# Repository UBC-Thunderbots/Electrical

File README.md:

# Electrical

Our repository for all things electrical! To get started, please see the [getting started document](docs/getting-started/getting-started.md).

If you are already set up, go to the [electrical system overview](docs/getting-started/board-overview.md).

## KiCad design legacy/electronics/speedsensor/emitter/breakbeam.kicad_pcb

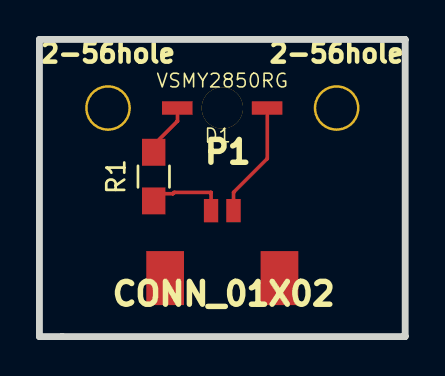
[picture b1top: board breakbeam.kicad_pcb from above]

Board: 2 copper layers, 20.3 x 16.5 mm, 5 parts (0 on the bottom side), 3 nets.

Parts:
2-56hole, 2-56hole#2: P***; 2-56hole
D1: VSMY2850RG; LED-VSMY2850RG
P1: CONN_01X02; connector_0_49_in_2pin
R1: 16.5R; R_0805_HandSoldering

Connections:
/3.3v: P1.1, R1.1
/GND: D1.1, P1.2
unnamed: D1.2, R1.2

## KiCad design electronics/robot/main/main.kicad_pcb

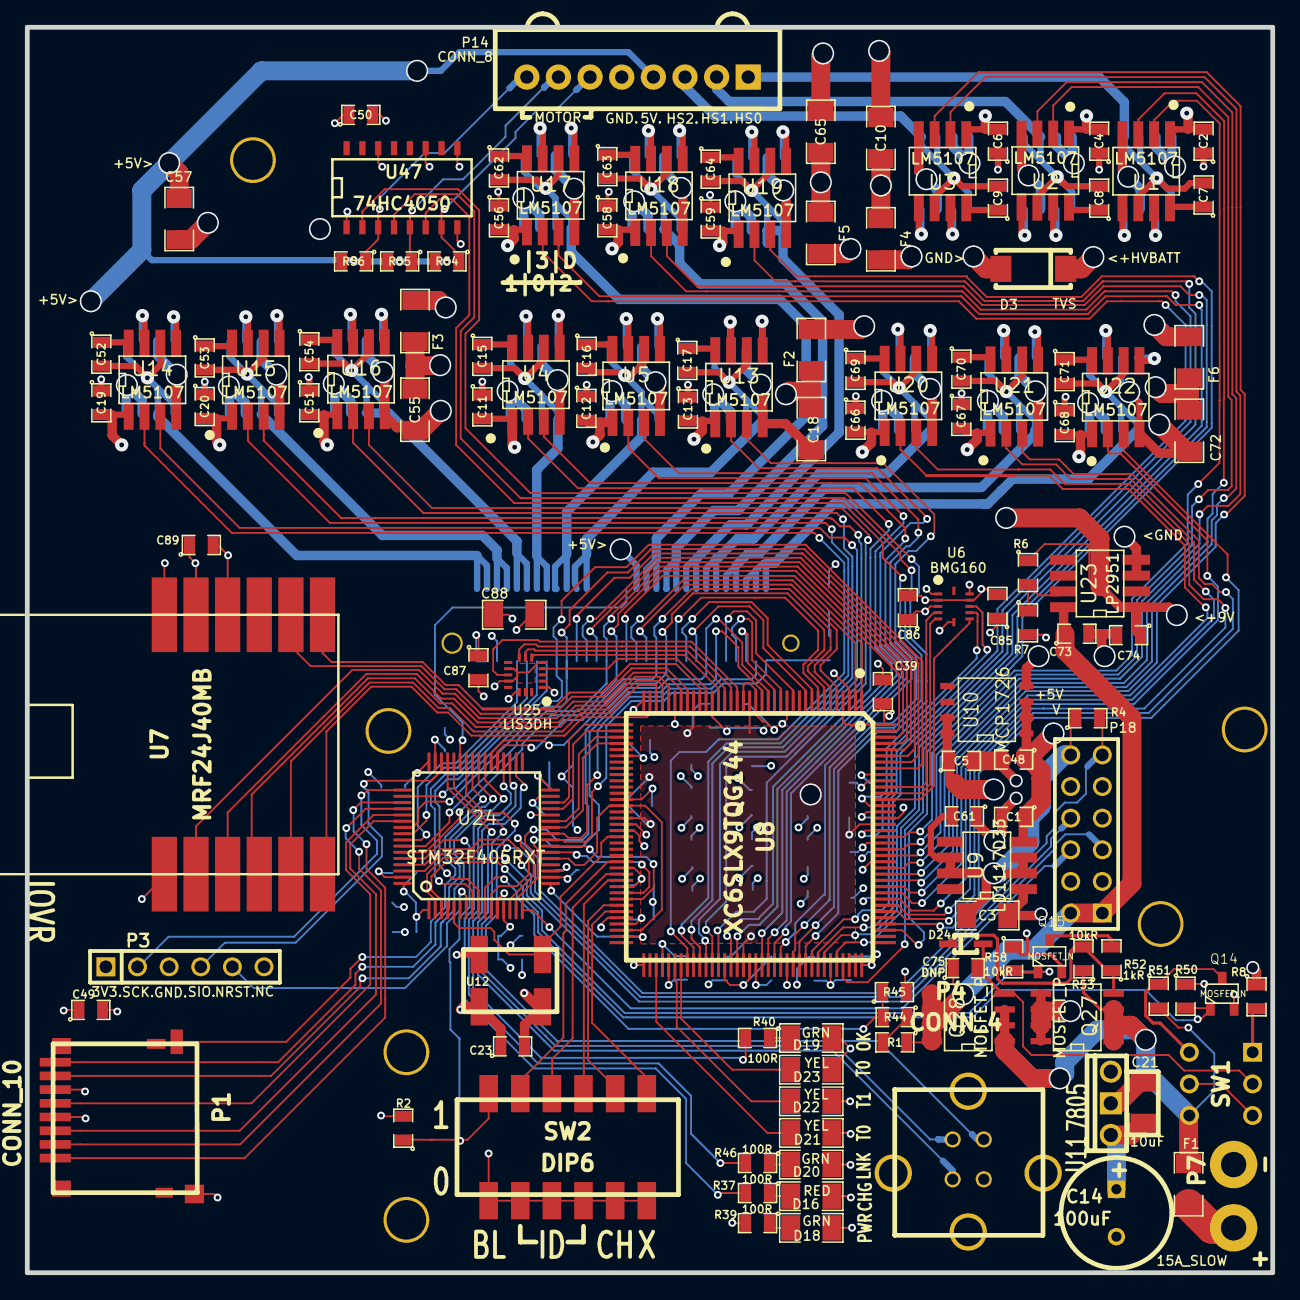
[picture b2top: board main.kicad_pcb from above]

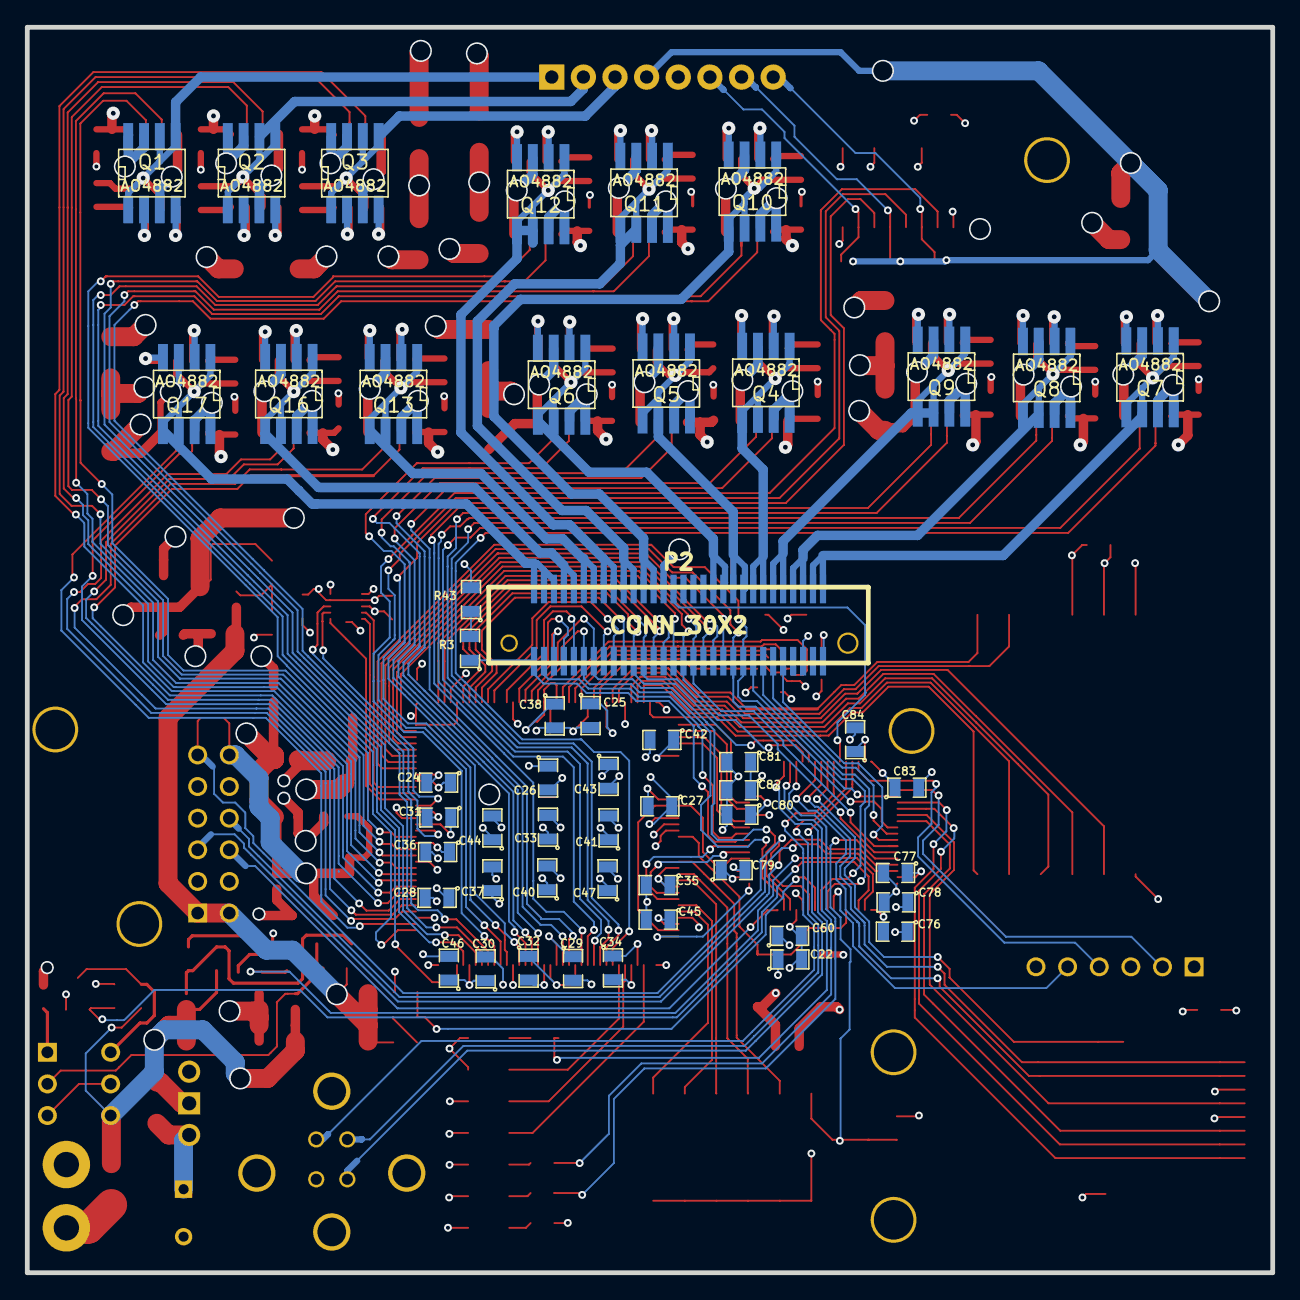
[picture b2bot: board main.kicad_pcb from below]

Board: 4 copper layers, 100.0 x 100.0 mm, 186 parts (52 on the bottom side), 210 nets.

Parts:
C1, C2, C4, C6, C7, C8, C9, C11, C12, C13, C15, C16, C17, C19, C20, C22, C23, C49, C50, C51, C52, C53, C54, C56, C58, C59, C61, C62, C63, C64, C66, C67, C68, C69, C70, C71, C76, C77, C79, C81, C83, C85, C86, C87, C89: 100nF; SM0805
C3, C10, C18, C21, C55, C57, C65, C72, C88: 10uF; SM1206
C5, C48, C73, C74, C75: 1uF; SM0805
C14: 100uF; C1.5V8V
C24, C25, C26, C27, C28, C29, C30, C32, C33, C34, C35, C37, C39, C41, C78, C82: 4.7uF; SM0805
C31, C36, C38, C40, C42, C43, C44, C45, C46, C47: 470nF; SM0805
C60: 10nF; SM0805
C80, C84: 2.2uF; SM0805
D3: TVS; DO-214AC
D16: RED; SM1206
D18, D19, D20: GRN; SM1206
D21, D22, D23: YEL; SM1206
D24: DIODESCH; SOD-323F
F1: 15A_SLOW; SM1206
F2, F3, F4, F5, F6: 5A; SM1206
M1, M2, M3: 5mm; M3_MOUNT
M4, M5, M6: 16mm; M3_MOUNT
P1: CONN_10; 114-00841-68
P2: CONN_30X2; FX6-60S-0.8SV
P3: CONN_6; PIN_ARRAY-6X1
P4: CONN_4; USB_B_V
P7: CONN_2; BATTERY_INLET
P14: CONN_8; EC16
P18: CONN_12; pin_array_6x2
Q1, Q2, Q3, Q4, Q5, Q6, Q7, Q8, Q9, Q10, Q11, Q12, Q13, Q16, Q17: AO4882; SO8E
Q14, Q15: MOSFET_N; SOT23_3GDS
Q27, Q28: MOSFET_P; SO8E-IRF9310
R1, R44, R50, R51, R53, R54, R55, R56, R58: 10kR; SM0805
R2, R7, R52: 1kR; SM0805
R3, R37, R39, R40, R43, R46: 100R; SM0805
R4: 100kR; SM0805
R6: 6kR; SM0805
R8: 1MR; SM0805
R45: 2.2kR; SM0805
SW1: SP3T; A27xP
SW2: DIP6; 219-6MST
U1, U2, U3, U4, U5, U13, U14, U15, U16, U17, U18, U19, U20, U21, U22: LM5107; SO8E
U6: BMG160; LGA12
U7: MRF24J40MB; MRF24J40M
U8: XC6SLX9TQG144; TQFP144
U9: LD1117D33; SO8E
U10: MCP1726; SO8N
U11: 7805; LM78XX_VERT
U12: ECS-3953M
U23: LP2951; SO8E
U24: STM32F405RXT; TQFP_64
U25: LIS3DH; LGA16
U47: 74HC4050; SO16N

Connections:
+1.2V: C5.1, C25.1, C27.1, C29.1, C31.1, U8.19, U8.28, U8.52, U8.89, U8.128, U10.7, U10.8
+3.3V: C3.1, C22.2, C23.1, C24.1, C26.1, C28.1, C30.1, C32.1, C33.1, C34.1, C35.1, C36.1, C37.1, C38.1, C39.1, C40.1, C41.1, C42.1, C43.1, C44.1, C45.1, C46.1, C47.1, C49.1, C50.1, C60.2, C61.2, C76.2, C77.2, C78.2, C79.2, C81.1, C82.1, C83.1, C85.2, C86.2, C87.2, C88.2, C89.2, P1.4, P1.9, P2.5, P3.1, P18.12, R4.1, R39.2, R43.2, SW2.1, SW2.2, SW2.3, SW2.4, SW2.5, SW2.6, U6.2, U6.10, U7.10, U8.4, U8.18, U8.20, U8.31, U8.36, U8.42, U8.53, U8.60, U8.63, U8.69, U8.76, U8.86, U8.90, U8.103, U8.122, U8.125, U8.129, U8.135, U8.144, U9.2, U9.3, U9.6, U9.7, U12.1, U12.4, U24.1, U24.13, U24.19, U24.32, U24.48, U24.64, U25.1, U25.14, U47.1
+5V: C1.1, C48.1, C57.2, P2.34, P14.4, R54.2, R55.2, R56.2, U9.4, U10.1, U10.2, U10.3, U11.VO
+9V: C2.2, C4.2, C6.2, C11.2, C12.2, C13.2, C19.2, C20.2, C51.2, C56.2, C58.2, C59.2, C66.2, C67.2, C68.2, C74.1, R6.1, U1.1, U2.1, U3.1, U4.1, U5.1, U13.1, U14.1, U15.1, U16.1, U17.1, U18.1, U19.1, U20.1, U21.1, U22.1, U23.1
+BATT: C14.1, C21.1, C73.1, C75.1, P18.1, P18.2, Q28.D, R1.1, U11.VI, U23.8
+HVBATT: D3.2, F2.1, F3.1, F4.1, F5.1, F6.1, Q27.D
/breakoutconn/BB_SENSOR: P2.59, R3.1, U24.24
/breakoutconn/LASER_DRIVE: P2.32, U24.43
/breakoutconn/LPS_DRIVE0: P2.15, U24.9
/breakoutconn/LPS_DRIVE1: P2.13, U24.8
/breakoutconn/LPS_DRIVE2: P2.11, U24.56
/breakoutconn/LPS_DRIVE3: P2.9, U24.57
/breakoutconn/LPS_SENSOR: P2.57, U24.25
/breakoutconn/M0_ENCODER0: P2.17, U8.137, U24.50
/breakoutconn/M0_ENCODER1: P2.19, U8.138, U24.55
/breakoutconn/M0_HALL0: P2.23, U8.140
/breakoutconn/M0_HALL1: P2.25, U8.141
/breakoutconn/M0_HALL2: P2.21, U8.139
/breakoutconn/M1_ENCODER0: P2.27, U8.142, U24.58
/breakoutconn/M1_ENCODER1: P2.29, U8.143, U24.59
/breakoutconn/M1_HALL0: P2.33, U8.2
/breakoutconn/M1_HALL1: P2.35, U8.5
/breakoutconn/M1_HALL2: P2.31, U8.1
/breakoutconn/M2_ENCODER0: P2.37, U8.6, U24.37
/breakoutconn/M2_ENCODER1: P2.39, U8.7, U24.38
/breakoutconn/M2_HALL0: P2.43, U8.9
/breakoutconn/M2_HALL1: P2.45, U8.10
/breakoutconn/M2_HALL2: P2.41, U8.8
/breakoutconn/M3_ENCODER0: P2.47, U8.16, U24.14
/breakoutconn/M3_ENCODER1: P2.49, U8.17, U24.15
/breakoutconn/M3_HALL0: P2.53, U8.14
/breakoutconn/M3_HALL1: P2.55, U8.15
/breakoutconn/M3_HALL2: P2.51, U8.12
/chicker/CHARGE: P18.5, U24.61
/fpga//MRF_CS: U7.8, U8.29
/fpga//MRF_RESET: U7.2, U8.30
/fpga/ACCEL_CLK: U8.26, U25.4
/fpga/ACCEL_INT: U8.21, U25.11
/fpga/ACCEL_MISO: U8.23, U25.7
/fpga/ACCEL_MOSI: U8.24, U25.6
/fpga/DONE: U8.71, U24.17
/fpga/GYRO_CLK: U6.7, U8.132
/fpga/GYRO_INT: U6.4, U8.134
/fpga/GYRO_MISO: U6.8, U8.131
/fpga/GYRO_MOSI: U6.9, U8.127
/fpga/ICB_CLK: U8.50, U8.70, U24.21
/fpga/ICB_IRQ: U8.40, U24.26
/fpga/ICB_MISO: U8.64, U24.22
/fpga/ICB_MOSI: U8.65, U24.23
/fpga/INIT_B: U8.39, U24.27
/fpga/LED_T0: D21.1, U8.75
/fpga/LED_T1: D22.1, U8.78
/fpga/LED_T2: D23.1, U8.79
/fpga/M4_HALL0: U8.97, U47.6
/fpga/M4_HALL1: U8.98, U47.4
/fpga/M4_HALL2: U8.99, U47.2
/fpga/MRF_CLK: U7.6, U8.35
/fpga/MRF_INT: U7.4, U8.33
/fpga/MRF_MISO: U7.7, U8.27
/fpga/MRF_MOSI: U7.5, U8.34
/fpga/MRF_WAKE: U7.3, U8.32
/fpga/OSC: U8.55, U12.3, U24.5
/fpga/PROG_B: U8.37, U24.30
/fpga/SW1: SW2.11, U8.59
/fpga/SW2: SW2.10, U8.61
/fpga/SW3: SW2.9, U8.62
/fpga/SW4: SW2.8, U8.66
/fpga/SW5: SW2.7, U8.67
/fpga/~ACCEL_CS: U8.22, U25.8
/fpga/~GYRO_CS: U6.5, U8.133
/fpga/~ICB_CS: U8.38, U24.29
/microcontroller/BATTERY: R44.2, R45.1, U24.10
/microcontroller/BOOT0: R2.1, SW2.12, U24.60
/microcontroller/CHICKER_CHIP: P18.6, U24.16
/microcontroller/CHICKER_KICK: P18.8, U24.62
/microcontroller/CHICKER_VOLTAGE: P18.11, R4.2, U24.11
/microcontroller/HV_PWR: Q15.G, R58.2, U24.2
/microcontroller/LED_C: R37.2, U24.36
/microcontroller/LED_L: R46.2, U24.35
/microcontroller/LED_S: R40.2, U24.34
/microcontroller/LOGIC_PWR: Q14.G, R50.2, U24.3
/microcontroller/NRST: P3.5, U24.7
/microcontroller/SD_CD: P1.10, U24.41
/microcontroller/SD_CK: P1.5, U24.53
/microcontroller/SD_CMD: P1.3, U24.54
/microcontroller/SD_D0: P1.7, U24.39
/microcontroller/SD_D1: P1.8, U24.40
/microcontroller/SD_D2: P1.1, U24.51
/microcontroller/SD_D3: P1.2, U24.52
/microcontroller/SWDCK: P3.2, U24.49
/microcontroller/SWDIO: P3.4, U24.46
/microcontroller/USB_DM: P4.2, U24.44
/microcontroller/USB_DP: P4.3, U24.45
/microcontroller/USB_VBUS: P4.1, U24.42
/microcontroller/VCAP1: C80.1, U24.31
/microcontroller/VCAP2: C84.1, U24.47
/motordriver0/HB0: C15.1, U4.8
/motordriver0/HB1: C16.1, U5.8
/motordriver0/HB2: C17.1, U13.8
/motordriver0/HG0: Q4.2, U4.7
/motordriver0/HG1: Q5.2, U5.7
/motordriver0/HG2: Q6.2, U13.7
/motordriver0/HIGH0: U4.2, U8.87
/motordriver0/HIGH1: U5.2, U8.88
/motordriver0/HIGH2: U8.92, U13.2
/motordriver0/HS0: C15.2, P2.14, P2.16, Q4.1, Q4.5, Q4.6, U4.6
/motordriver0/HS1: C16.2, P2.18, P2.20, Q5.1, Q5.5, Q5.6, U5.6
/motordriver0/HS2: C17.2, P2.22, P2.24, Q6.1, Q6.5, Q6.6, U13.6
/motordriver0/HV_BATT_F: C18.1, F2.2, Q4.7, Q4.8, Q5.7, Q5.8, Q6.7, Q6.8
/motordriver0/LG0: Q4.4, U4.5
/motordriver0/LG1: Q5.4, U5.5
/motordriver0/LG2: Q6.4, U13.5
/motordriver0/LOW0: U4.3, U8.93
/motordriver0/LOW1: U5.3, U8.94
/motordriver0/LOW2: U8.95, U13.3
/motordriver1/HB0: C52.1, U14.8
/motordriver1/HB1: C53.1, U15.8
/motordriver1/HB2: C54.1, U16.8
/motordriver1/HG0: Q7.2, U14.7
/motordriver1/HG1: Q8.2, U15.7
/motordriver1/HG2: Q9.2, U16.7
/motordriver1/HIGH0: U8.80, U14.2
/motordriver1/HIGH1: U8.81, U15.2
/motordriver1/HIGH2: U8.82, U16.2
/motordriver1/HS0: C52.2, P2.2, P2.4, Q7.1, Q7.5, Q7.6, U14.6
/motordriver1/HS1: C53.2, P2.6, P2.8, Q8.1, Q8.5, Q8.6, U15.6
/motordriver1/HS2: C54.2, P2.10, P2.12, Q9.1, Q9.5, Q9.6, U16.6
/motordriver1/HV_BATT_F: C55.1, F3.2, Q7.7, Q7.8, Q8.7, Q8.8, Q9.7, Q9.8
/motordriver1/LG0: Q7.4, U14.5
/motordriver1/LG1: Q8.4, U15.5
/motordriver1/LG2: Q9.4, U16.5
/motordriver1/LOW0: U8.83, U14.3
/motordriver1/LOW1: U8.84, U15.3
/motordriver1/LOW2: U8.85, U16.3
/motordriver2/HB0: C69.1, U20.8
/motordriver2/HB1: C70.1, U21.8
/motordriver2/HB2: C71.1, U22.8
/motordriver2/HG0: Q13.2, U20.7
/motordriver2/HG1: Q16.2, U21.7
/motordriver2/HG2: Q17.2, U22.7
/motordriver2/HIGH0: U8.118, U20.2
/motordriver2/HIGH1: U8.117, U21.2
/motordriver2/HIGH2: U8.116, U22.2
/motordriver2/HS0: C69.2, P2.48, P2.50, Q13.1, Q13.5, Q13.6, U20.6
/motordriver2/HS1: C70.2, P2.52, P2.54, Q16.1, Q16.5, Q16.6, U21.6
/motordriver2/HS2: C71.2, P2.56, P2.58, P2.60, Q17.1, Q17.5, Q17.6, U22.6
/motordriver2/HV_BATT_F: C72.1, F6.2, Q13.7, Q13.8, Q16.7, Q16.8, Q17.7, Q17.8
/motordriver2/LG0: Q13.4, U20.5
/motordriver2/LG1: Q16.4, U21.5
/motordriver2/LG2: Q17.4, U22.5
/motordriver2/LOW0: U8.115, U20.3
/motordriver2/LOW1: U8.114, U21.3
/motordriver2/LOW2: U8.112, U22.3
/motordriver3/HB0: C62.1, U17.8
/motordriver3/HB1: C63.1, U18.8
/motordriver3/HB2: C64.1, U19.8
/motordriver3/HG0: Q10.2, U17.7
/motordriver3/HG1: Q11.2, U18.7
/motordriver3/HG2: Q12.2, U19.7
/motordriver3/HIGH0: U8.100, U17.2
/motordriver3/HIGH1: U8.101, U18.2
/motordriver3/HIGH2: U8.102, U19.2
/motordriver3/HS0: C62.2, P2.36, P2.38, Q10.1, Q10.5, Q10.6, U17.6
/motordriver3/HS1: C63.2, P2.40, P2.42, Q11.1, Q11.5, Q11.6, U18.6
/motordriver3/HS2: C64.2, P2.44, P2.46, Q12.1, Q12.5, Q12.6, U19.6
/motordriver3/HV_BATT_F: C65.1, F5.2, Q10.7, Q10.8, Q11.7, Q11.8, Q12.7, Q12.8
/motordriver3/LG0: Q10.4, U17.5
/motordriver3/LG1: Q11.4, U18.5
/motordriver3/LG2: Q12.4, U19.5
/motordriver3/LOW0: U8.104, U17.3
/motordriver3/LOW1: U8.105, U18.3
/motordriver3/LOW2: U8.111, U19.3
/motordriver4/HB0: C7.1, U1.8
/motordriver4/HB1: C8.1, U2.8
/motordriver4/HB2: C9.1, U3.8
/motordriver4/HG0: Q1.2, U1.7
/motordriver4/HG1: Q2.2, U2.7
/motordriver4/HG2: Q3.2, U3.7
/motordriver4/HIGH0: U1.2, U8.126
/motordriver4/HIGH1: U2.2, U8.124
/motordriver4/HIGH2: U3.2, U8.123
/motordriver4/HS0: C7.2, P14.1, Q1.1, Q1.5, Q1.6, U1.6
/motordriver4/HS1: C8.2, P14.2, Q2.1, Q2.5, Q2.6, U2.6
/motordriver4/HS2: C9.2, P14.3, Q3.1, Q3.5, Q3.6, U3.6
/motordriver4/HV_BATT_F: C10.1, F4.2, Q1.7, Q1.8, Q2.7, Q2.8, Q3.7, Q3.8
/motordriver4/LG0: Q1.4, U1.5
/motordriver4/LG1: Q2.4, U2.5
/motordriver4/LG2: Q3.4, U3.5
/motordriver4/LOW0: U1.3, U8.121
/motordriver4/LOW1: U2.3, U8.120
/motordriver4/LOW2: U3.3, U8.119
/power/FUSE_IN: F1.1, P7.1
/power/FUSE_OUT: F1.2, Q27.S, Q28.S, R51.2, R53.1, SW1.6
GND: C1.2, C2.1, C3.2, C4.1, C5.2, C6.1, C10.2, C11.1, C12.1, C13.1, C14.2, C18.2, C19.1, C20.1, C21.2, C22.1, C23.2, C24.2, C25.2, C26.2, C27.2, C28.2, C29.2, C30.2, C31.2, C32.2, C33.2, C34.2, C35.2, C36.2, C37.2, C38.2, C39.2, C40.2, C41.2, C42.2, C43.2, C44.2, C45.2, C46.2, C47.2, C48.2, C49.2, C50.2, C51.1, C55.2, C56.1, C57.1, C58.1, C59.1, C60.1, C61.1, C65.2, C66.1, C67.1, C68.1, C72.2, C73.2, C74.2, C76.1, C77.1, C78.1, C79.1, C80.2, C81.2, C82.2, C83.2, C84.2, C85.1, C86.1, C87.1, C88.1, C89.1, D3.1, D16.2, D18.2, D19.2, D20.2, D21.2, D22.2, D23.2, P1.6, P2.1, P2.3, P3.3, P4.4, P7.2, P14.5, P18.3, P18.4, P18.9, P18.10, Q1.3, Q2.3, Q3.3, Q4.3, Q5.3, Q6.3, Q7.3, Q8.3, Q9.3, Q10.3, Q11.3, Q12.3, Q13.3, Q14.S, Q15.S, Q16.3, Q17.3, R2.2, R7.2, R8.1, R45.2, R50.1, R58.1, U1.4, U2.4, U3.4, U4.4, U5.4, U6.1, U6.3, U6.6, U6.11, U7.1, U7.11, U7.12, U8.3, U8.13, U8.25, U8.49, U8.54, U8.68, U8.73, U8.77, U8.91, U8.96, U8.108, U8.113, U8.130, U8.136, U9.1, U10.4, U11.GND, U12.2, U13.4, U14.4, U15.4, U16.4, U17.4, U18.4, U19.4, U20.4, U21.4, U22.4, U23.3, U23.4, U24.12, U24.18, U24.28, U24.63, U25.5, U25.10, U25.12, U47.8, U47.9, U47.11, U47.14
unnamed: R1.2, R44.1
unnamed: R3.2, R43.1
unnamed: R8.2, SW1.1
unnamed: D24.2, Q27.G, R52.1, R53.2
unnamed: R6.2, R7.1, U23.7
unnamed: Q15.D, R52.2
unnamed: SW1.3, SW1.5
unnamed: Q14.D, R51.1, SW1.4
unnamed: D18.1, R39.1
unnamed: C75.2, D24.1, Q28.G, SW1.2
unnamed: P14.8, R56.1, U47.3
unnamed: P14.6, R54.1, U47.7
unnamed: P14.7, R55.1, U47.5
unnamed: D19.1, R40.1
unnamed: D16.1, R37.1
unnamed: D20.1, R46.1

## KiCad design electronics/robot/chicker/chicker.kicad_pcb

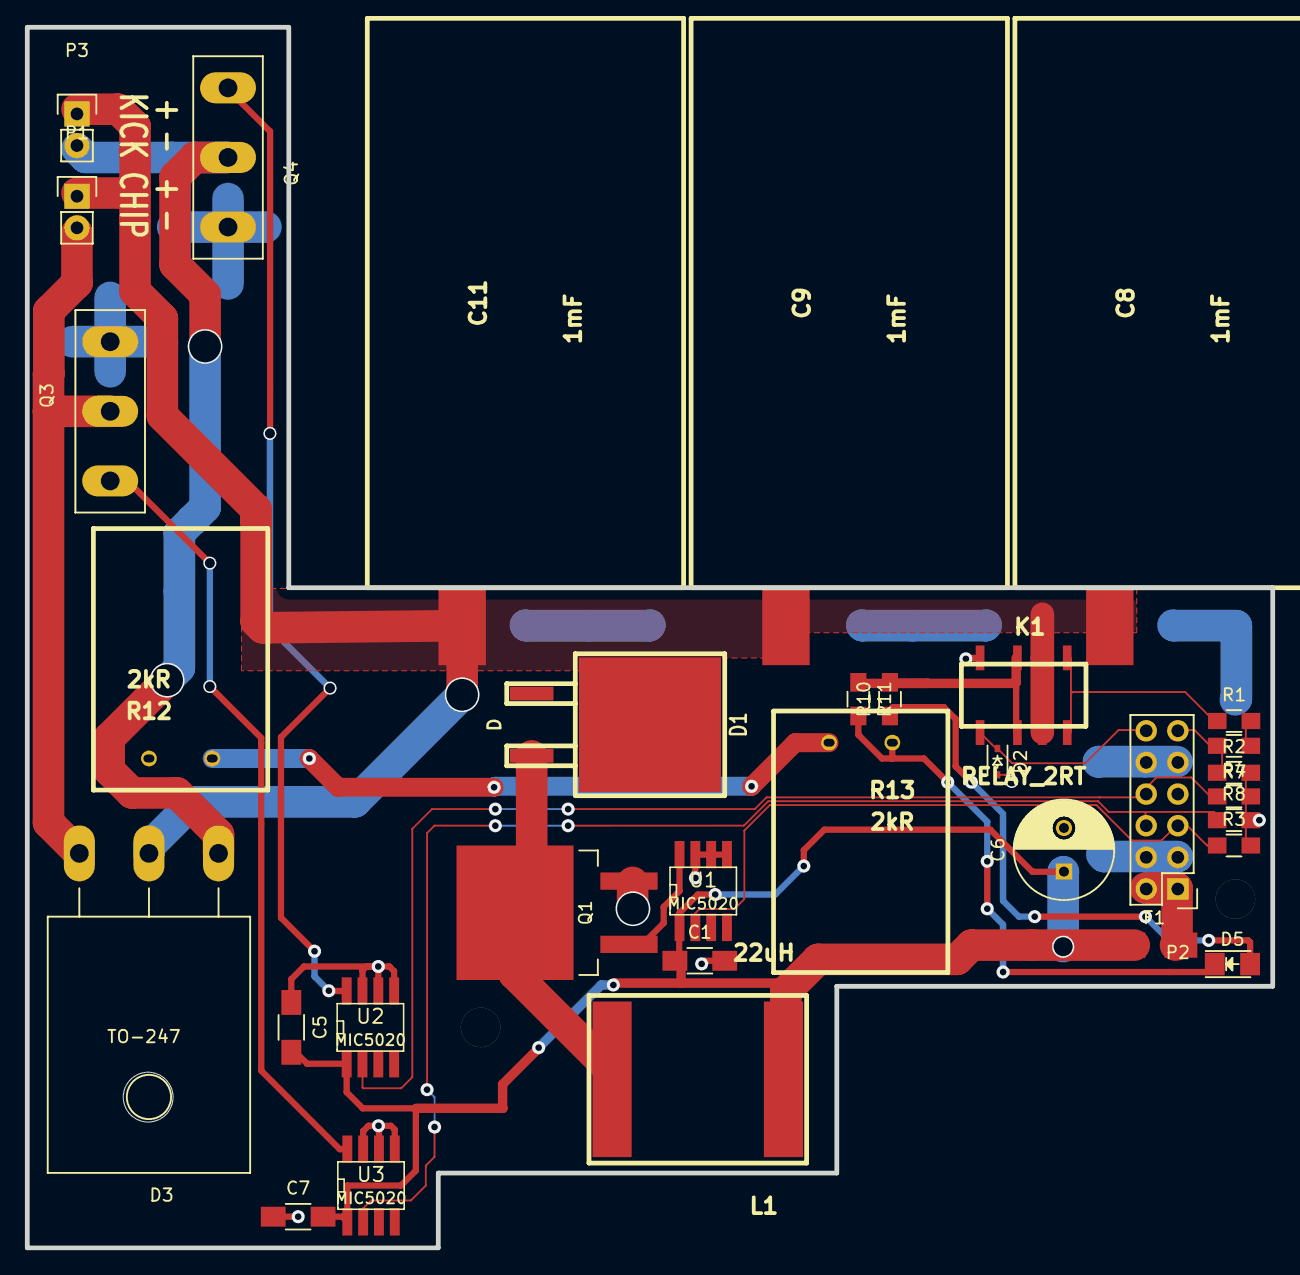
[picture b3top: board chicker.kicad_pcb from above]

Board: 2 copper layers, 100.0 x 98.0 mm, 35 parts (0 on the bottom side), 21 nets.

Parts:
C1, C5, C7: 10uF; C_1206_HandSoldering
C6: 100uF; C_Radial_D8_L11.5_P3.5
C8, C9, C11: 1mF; ESMQ251VSN102MQ45S_HORIZONTAL
D1: D; D2PAK-DIODE-BACKWARDS
D2: D_Schottky; SOD-323
D3: RURG3060CC; TO-247_Horizontal_Neutral123
D5: LED; LED_1206
F1: 5A; Fuse_SMD1206_HandSoldering
K1: RELAY_2RT; PB1163CT-ND
L1: 22uH; SRP1770TA
M1, M2: 16mm; M3_MOUNT
P1, P3: CONN_01X02; Pin_Header_Straight_1x02
P2: CONN_02X06; Pin_Header_Straight_2x06
Q1: Q_NMOS_GSD; TO-263-2Lead
Q3, Q4: Q_NIGBT_GCE; TO-247_Vertical_Neutral123
R1, R7: 100kR; R_0805_HandSoldering
R2: 2.2kR; R_0805_HandSoldering
R3, R4, R8: 10kR; R_0805_HandSoldering
R10, R11: 160R; R_0805_HandSoldering
R12, R13: 2kR; PF2203
U1, U2, U3: MIC5020; SO8E

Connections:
+BATT: C1.1, C5.2, C6.1, C7.2, F1.1, L1.1, U1.1, U2.1, U3.1
/CAP+: C8.1, C9.1, C11.1, D1.1, D3.2, K1.5, K1.12, P1.1, P3.1
/CHARGE: P2.5, R3.1, U1.2
/CHARGE_MOSFET_DRAIN: D1.2, L1.2, Q1.3
/CHIP: P2.6, R8.1, U3.2
/Chip-: D3.3, P1.2, Q3.2
/KICK: P2.8, R4.1, U2.2
/Kick-: D3.1, P3.2, Q4.2
GND: C1.2, C5.1, C6.2, C7.1, C8.2, C9.2, C11.2, D2.2, K1.8, P2.3, P2.4, P2.7, P2.9, P2.10, Q1.2, Q3.3, Q4.3, R2.2, R3.2, R4.2, R8.2, R12.1, U1.5, U1.6, U1.7, U2.5, U2.6, U2.7, U3.5, U3.6, U3.7
unnamed: D2.1, K1.9, P2.12
unnamed: D5.1, R11.2, R13.1
unnamed: D5.2, R10.1
unnamed: F1.2, P2.1, P2.2
unnamed: K1.1, K1.16, R1.1
unnamed: K1.3, K1.14, R10.2, R11.1
unnamed: P2.11, R2.1, R7.2
unnamed: Q1.1, U1.8
unnamed: Q3.1, U3.8
unnamed: Q4.1, U2.8
unnamed: R1.2, R7.1
unnamed: R12.2, R13.2

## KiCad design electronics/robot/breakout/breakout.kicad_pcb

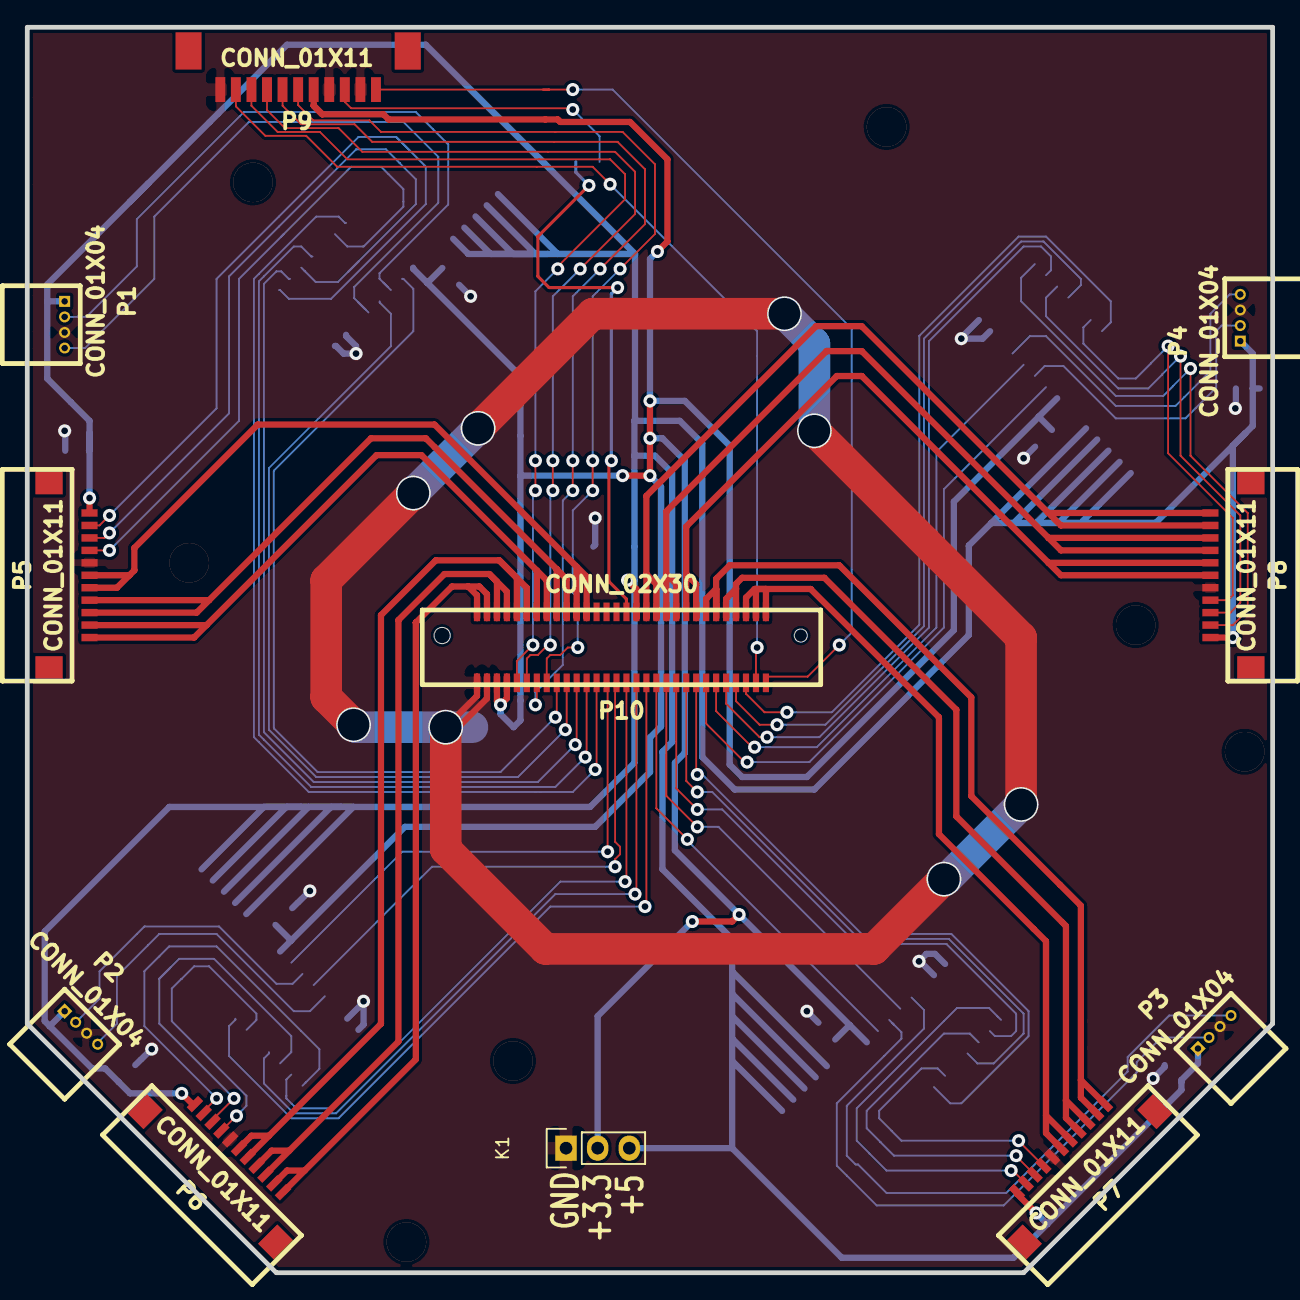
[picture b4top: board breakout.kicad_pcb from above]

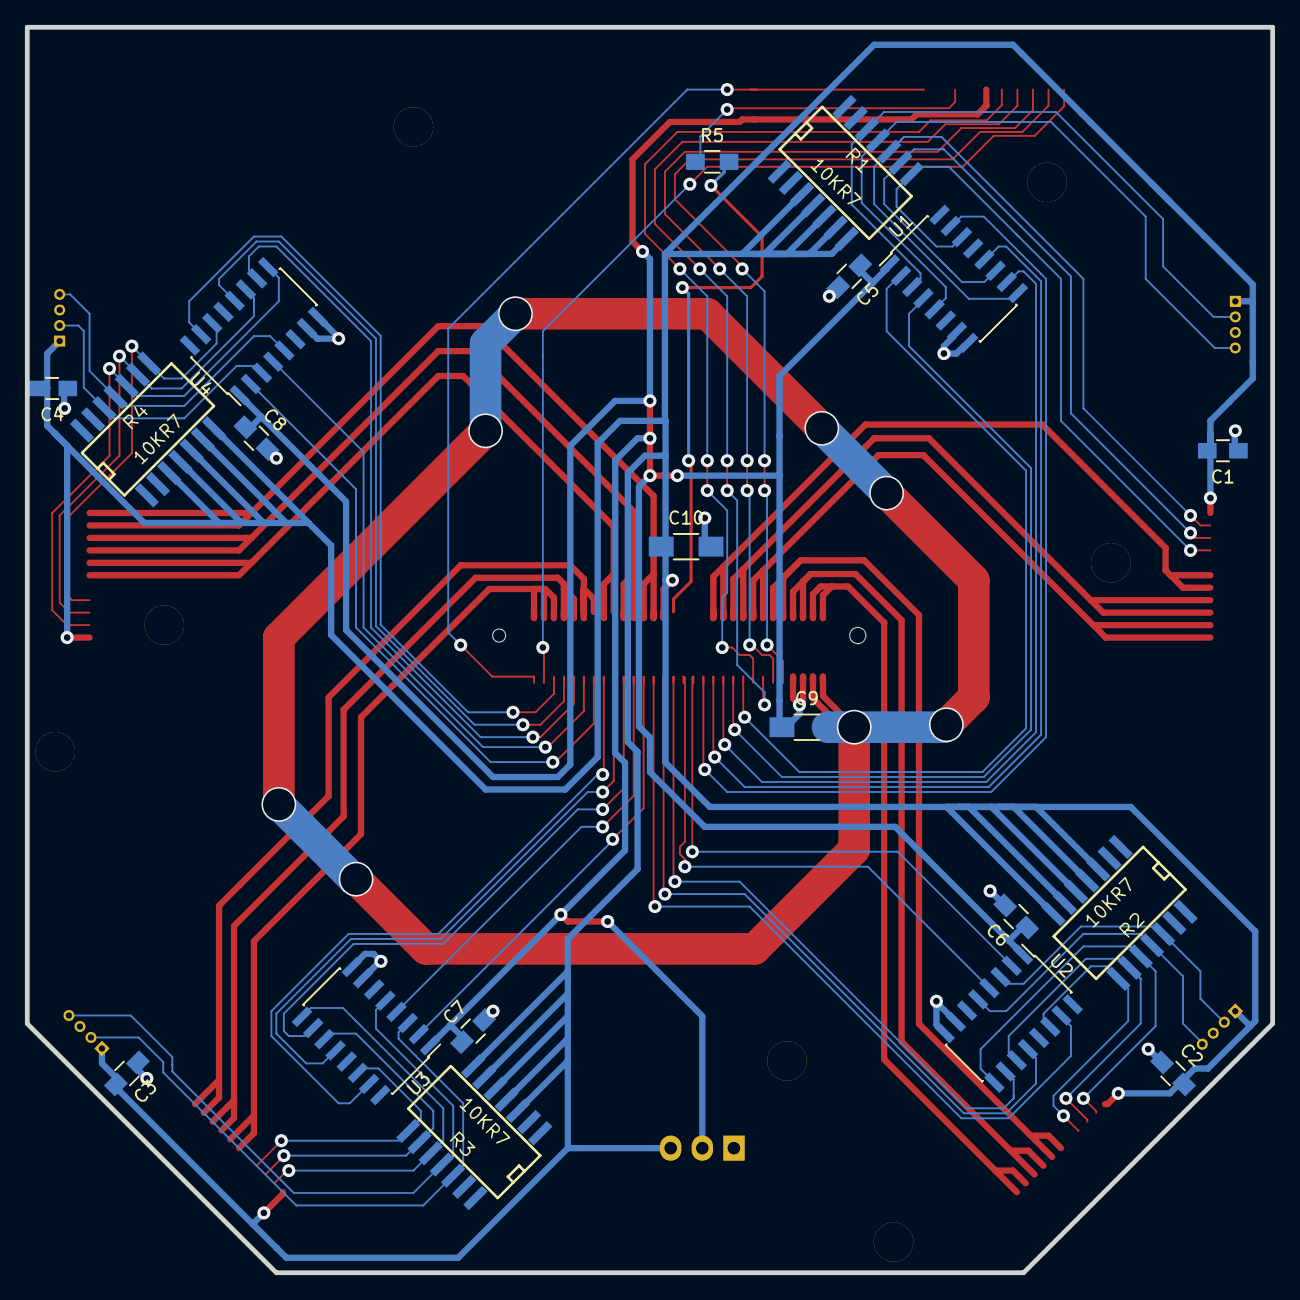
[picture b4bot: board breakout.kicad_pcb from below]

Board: 2 copper layers, 100.0 x 100.0 mm, 37 parts (19 on the bottom side), 63 nets.

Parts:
C1, C2, C3, C4, C5, C6, C7, C8: 100nF; C_0805_HandSoldering
C9, C10: 10uF; C_1206_HandSoldering
K1: CONN_01X03; Pin_Header_Straight_1x03
M1, M2, M3, M4, M5, M6, M7: 5mm; M3_MOUNT
P1, P2, P3, P4: CONN_01X04; 53048-0410
P5, P6, P7, P8: CONN_01X11; FH12-11S-1SH
P9: CONN_01X11; WM7629CT-ND
P10: CONN_02X30; FX6-60P-0.8SV
R1, R2, R3, R4: 10KR7; SO14HUGE
R5: 100R; R_0805_HandSoldering
U1, U2, U3, U4: 74HC4050; SOIC-16_3.9x9.9mm_Pitch1.27mm_HandSoldering

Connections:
+3V3: C5.1, C6.1, C7.1, C8.1, C9.1, K1.2, P9.5, P10.5, P10.7, U1.1, U2.1, U3.1, U4.1
+5V: C1.2, C2.2, C3.2, C4.2, C10.1, K1.3, P1.1, P2.1, P3.1, P4.1, P5.1, P6.1, P7.1, P8.1, P10.34, R1.3, R1.4, R1.5, R1.6, R1.7, R2.3, R2.4, R2.5, R2.6, R2.7, R3.3, R3.4, R3.5, R3.6, R3.7, R4.3, R4.4, R4.5, R4.6, R4.7
/M0_PHASE0: P5.10, P5.11, P10.14, P10.16
/M0_PHASE1: P5.8, P5.9, P10.18, P10.20
/M0_PHASE2: P5.6, P5.7, P10.22, P10.24
/M0_SENSOR0: P10.23, U1.12
/M0_SENSOR1: P10.25, U1.15
/M0_SENSOR2: P10.21, U1.10
/M0_SENSOR3: P10.17, U1.2
/M0_SENSOR4: P10.19, U1.4
/M1_PHASE0: P6.10, P6.11, P10.2, P10.4
/M1_PHASE1: P6.8, P6.9, P10.6, P10.8
/M1_PHASE2: P6.6, P6.7, P10.10, P10.12
/M1_SENSOR0: P10.33, U2.12
/M1_SENSOR1: P10.35, U2.15
/M1_SENSOR2: P10.31, U2.10
/M1_SENSOR3: P10.27, U2.2
/M1_SENSOR4: P10.29, U2.4
/M2_PHASE0: P7.10, P7.11, P10.48, P10.50
/M2_PHASE1: P7.8, P7.9, P10.52, P10.54
/M2_PHASE2: P7.6, P7.7, P10.56, P10.58, P10.60
/M2_SENSOR0: P10.43, U3.12
/M2_SENSOR1: P10.45, U3.15
/M2_SENSOR2: P10.41, U3.10
/M2_SENSOR3: P10.37, U3.2
/M2_SENSOR4: P10.39, U3.4
/M3_PHASE0: P8.10, P8.11, P10.36, P10.38
/M3_PHASE1: P8.8, P8.9, P10.40, P10.42
/M3_PHASE2: P8.6, P8.7, P10.44, P10.46
/M3_SENSOR0: P10.53, U4.12
/M3_SENSOR1: P10.55, U4.15
/M3_SENSOR2: P10.51, U4.10
/M3_SENSOR3: P10.47, U4.2
/M3_SENSOR4: P10.49, U4.4
GND: C1.1, C2.1, C3.1, C4.1, C5.2, C6.2, C7.2, C8.2, C9.2, C10.2, K1.1, P1.3, P2.3, P3.3, P4.3, P5.5, P6.5, P7.5, P8.5, P9.2, P9.4, P9.11, P10.1, P10.3, U1.7, U1.8, U2.7, U2.8, U3.7, U3.8, U4.7, U4.8
unnamed: P1.2, R1.12, U1.3
unnamed: P1.4, R1.11, U1.5
unnamed: P2.2, R2.12, U2.3
unnamed: P2.4, R2.11, U2.5
unnamed: P3.2, R3.12, U3.3
unnamed: P3.4, R3.11, U3.5
unnamed: P4.2, R4.12, U4.3
unnamed: P4.4, R4.11, U4.5
unnamed: P5.2, R1.10, U1.9
unnamed: P5.3, R1.9, U1.11
unnamed: P5.4, R1.8, U1.14
unnamed: P6.2, R2.10, U2.9
unnamed: P6.3, R2.9, U2.11
unnamed: P6.4, R2.8, U2.14
unnamed: P7.2, R3.10, U3.9
unnamed: P7.3, R3.9, U3.11
unnamed: P7.4, R3.8, U3.14
unnamed: P8.2, R4.10, U4.9
unnamed: P8.3, R4.9, U4.11
unnamed: P8.4, R4.8, U4.14
unnamed: P9.3, R5.1
unnamed: P9.9, P10.9
unnamed: P9.8, P10.11
unnamed: P9.7, P10.13
unnamed: P9.6, P10.15
unnamed: P10.32, R5.2
unnamed: P9.10, P10.57
unnamed: P9.1, P10.59

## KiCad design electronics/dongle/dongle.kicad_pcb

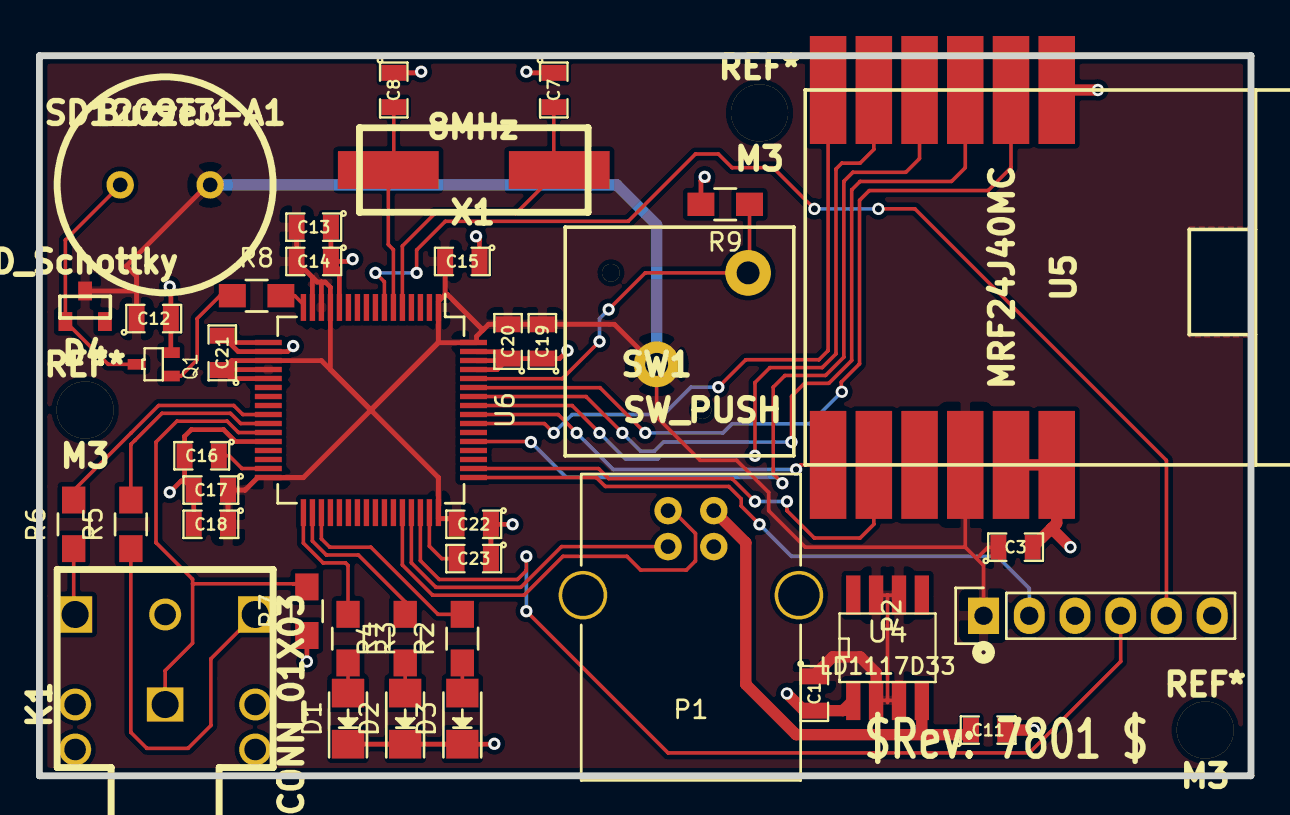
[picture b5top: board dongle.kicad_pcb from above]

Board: 2 copper layers, 67.3 x 40.0 mm, 39 parts (0 on the bottom side), 34 nets.

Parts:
Buzzer1: SD1209T3-A1; Buzzer
C1, C16, C23: 2.2uF; SM0805
C3, C15, C17, C20, C21, C22: 100nF; SM0805
C7, C8: 15pF; SM0805
C11, C12, C13: 1uF; SM0805
C14: 10nF; SM0805
C18, C19: 4.7uF; SM0805
D1, D2, D3: LED; LED-1206
D4: D_Schottky; SOT23DIODE
K1: CONN_01X03; SJ1-3523N
P1: USB_B
P2: CONN_01X06; Pin_Header_Straight_1x06
Q1: BC847A; SOT323-transistor
R2, R3, R4, R5, R6: 100R; R_0805_HandSoldering
R7: 2.2kR; R_0805_HandSoldering
R8, R9: 1kR; R_0805_HandSoldering
SW1: SW_PUSH; ESWITCH_320.01
U4: LD1117D33; SO8E
U5: MRF24J40MC; MRF24J40M
U6: STM32F405RXT; TQFP-64_10x10mm_Pitch0.5mm
X1: 8MHz; HC49US

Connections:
+3V3: Buzzer1.1, C1.1, C3.1, C12.1, C13.2, C14.2, C15.2, C17.1, C18.1, C19.2, C20.2, C21.1, C22.2, D4.1, P2.1, SW1.2, U4.2, U4.3, U4.6, U4.7, U5.10, U6.1, U6.13, U6.14, U6.15, U6.19, U6.20, U6.21, U6.32, U6.48, U6.64
+5V: C11.1, P1.1, U4.4
/NRST: P2.5, U6.7
/SWCLK: P2.2, U6.49
/SWDIO: P2.4, U6.46
GND: C1.2, C3.2, C7.1, C8.1, C11.2, C12.2, C13.1, C14.1, C15.1, C16.2, C17.2, C18.2, C19.1, C20.1, C21.2, C22.1, C23.1, D1.1, D2.1, D3.1, P1.4, P1.5, P2.3, Q1.E, R7.1, R9.2, U4.1, U5.1, U5.11, U5.12, U6.12, U6.17, U6.18, U6.28, U6.61, U6.62, U6.63
unnamed: Buzzer1.2, D4.2, Q1.C
unnamed: C7.2, U6.5, X1.1
unnamed: C8.2, U6.6, X1.2
unnamed: C16.1, U6.31
unnamed: C23.2, U6.47
unnamed: D1.2, R3.2
unnamed: D2.2, R4.1
unnamed: D3.2, R2.1
unnamed: K1.1, R7.2, U6.27
unnamed: K1.2, R5.1
unnamed: K1.3, R6.1
unnamed: P1.2, U6.44
unnamed: P1.3, U6.45
unnamed: Q1.B, R8.1
unnamed: R2.2, U6.35
unnamed: R3.1, U6.33
unnamed: R4.2, U6.34
unnamed: R5.2, U6.26
unnamed: R6.2, U6.25
unnamed: R8.2, U6.16
unnamed: R9.1, SW1.1, U6.60
unnamed: U5.2, U6.59
unnamed: U5.3, U6.58
unnamed: U5.4, U6.53
unnamed: U5.5, U6.57
unnamed: U5.6, U6.55
unnamed: U5.7, U6.56
unnamed: U5.8, U6.50

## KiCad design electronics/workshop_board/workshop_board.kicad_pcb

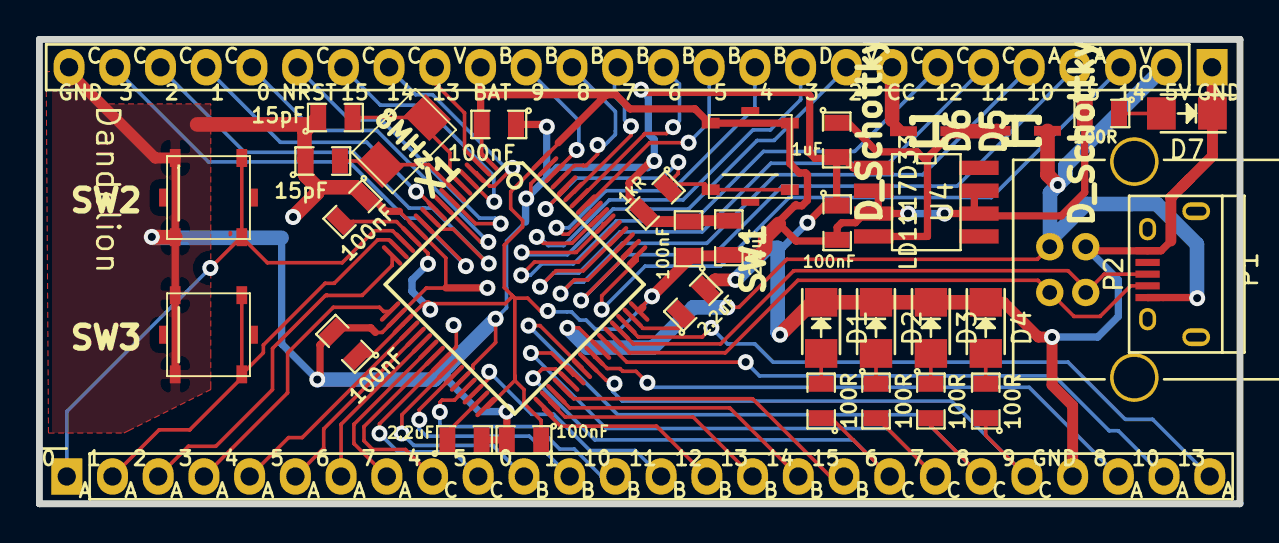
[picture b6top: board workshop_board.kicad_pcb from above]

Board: 2 copper layers, 66.7 x 25.8 mm, 35 parts (0 on the bottom side), 63 nets.

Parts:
C1, C3, C4: 2.2uF; SM0805
C7, C8: 15pF; SM0805
C11: 1uF; SM0805
C13, C15, C17, C20, C21, C22: 100nF; SM0805
D1, D7: GRN; LED-1206
D2: YEL; LED-1206
D3: RED; LED-1206
D4: BLU; LED-1206
D5, D6: D_Schottky; SOD-323F
P1: USB_B
P2: USB_OTG; USB_Micro-B
R1, R2, R3, R4, R8: 100R; SM0805
R5: 1kR; SM0805
SW1, SW2, SW3: SW_PUSH; SW_SMD_TAC
U1: CONN_26_LEFT; Pin_Header_Straight_1x26
U2: STM32F405RXT_fat; TQFP_64
U3: CONN_26_RIGHT; Pin_Header_Straight_1x26
U4: LD1117D33; SO8E
X1: 8MHz; CRYSTAL_5x3.2

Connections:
+3V3: C1.1, C13.2, C15.2, C17.1, C20.2, C21.1, C22.1, R8.2, SW1.2, U1.17, U2.1, U2.13, U2.19, U2.32, U2.48, U2.64, U4.2, U4.3, U4.6, U4.7
+5V: D6.2, P1.1, P2.1, U1.2, U2.42
GND: C1.2, C3.2, C4.2, C7.1, C8.1, C11.2, C13.1, C15.1, C17.2, C20.1, C21.2, C22.2, D1.1, D2.1, D3.1, D4.1, D7.1, P1.4, P2.5, R5.2, SW2.1, SW3.1, U1.1, U1.26, U2.12, U2.18, U2.28, U2.63, U3.23, U4.1
unnamed: C3.1, U2.31
unnamed: C4.1, U2.47
unnamed: C7.2, U2.5, X1.1
unnamed: C8.2, U2.6, X1.2
unnamed: C11.1, D5.1, D6.1, U4.4
unnamed: D1.2, R1.2
unnamed: D2.2, R2.1
unnamed: D3.2, R3.1
unnamed: D4.2, R4.2
unnamed: D5.2, U1.8
unnamed: D7.2, R8.1
unnamed: P1.2, P2.2, U2.44
unnamed: P1.3, P2.3, U2.45
unnamed: R1.1, U2.37, U3.19
unnamed: R2.2, U2.38, U3.20
unnamed: R3.2, U2.39, U3.21
unnamed: R4.1, U2.40, U3.22
unnamed: R5.1, SW1.1, U2.60
unnamed: SW2.2, U2.14, U3.1
unnamed: SW3.2, U2.15, U3.2
unnamed: U1.3, U2.49
unnamed: U1.4, U2.50
unnamed: U1.5, U2.51
unnamed: U1.6, U2.52
unnamed: U1.7, U2.53
unnamed: U1.9, U2.54
unnamed: U1.10, U2.55
unnamed: U1.11, U2.56
unnamed: U1.12, U2.57
unnamed: U1.13, U2.58
unnamed: U1.14, U2.59
unnamed: U1.15, U2.61
unnamed: U1.16, U2.62
unnamed: U1.18, U2.2
unnamed: U1.19, U2.3
unnamed: U1.20, U2.4
unnamed: U1.21, U2.7
unnamed: U1.22, U2.8
unnamed: U1.23, U2.9
unnamed: U1.24, U2.10
unnamed: U1.25, U2.11
unnamed: U2.16, U3.3
unnamed: U2.17, U3.4
unnamed: U2.20, U3.5
unnamed: U2.21, U3.6
unnamed: U2.22, U3.7
unnamed: U2.23, U3.8
unnamed: U2.24, U3.9
unnamed: U2.25, U3.10
unnamed: U2.26, U3.11
unnamed: U2.27, U3.12
unnamed: U2.29, U3.13
unnamed: U2.30, U3.14
unnamed: U2.33, U3.15
unnamed: U2.34, U3.16
unnamed: U2.35, U3.17
unnamed: U2.36, U3.18
unnamed: U2.41, U3.24
unnamed: U2.43, U3.25
unnamed: U2.46, U3.26

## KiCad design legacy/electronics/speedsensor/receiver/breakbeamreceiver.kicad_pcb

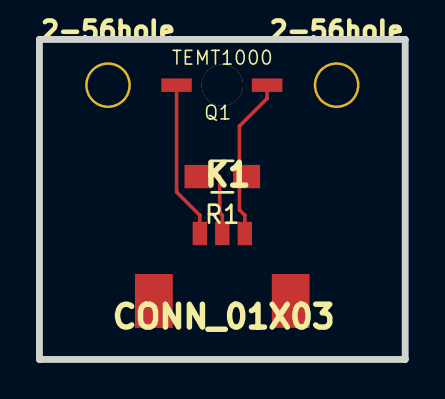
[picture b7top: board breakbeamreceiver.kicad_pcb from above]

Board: 2 copper layers, 20.3 x 17.8 mm, 5 parts (0 on the bottom side), 3 nets.

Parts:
2-56hole, 2-56hole#2: P***; 2-56hole
K1: CONN_01X03; connector_0_49_in_3pin
Q1: TEMT1000; PHOTOTRANS-TEMT1000
R1: 100R; R_0805_HandSoldering

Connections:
/3.3v: K1.1, Q1.3
/GND: K1.2, R1.2
/SIG: K1.3, Q1.1, R1.1
